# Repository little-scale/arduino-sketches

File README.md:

# arduino-sketches
Arduino and Teensy-based Sketches

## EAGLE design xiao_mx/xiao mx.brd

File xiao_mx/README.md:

A simple, small USB MIDI device using the Seed Studio Xiao M0, the Adafruit Tinyusb library, 5 pots and 6 unstablised mx cherry switches

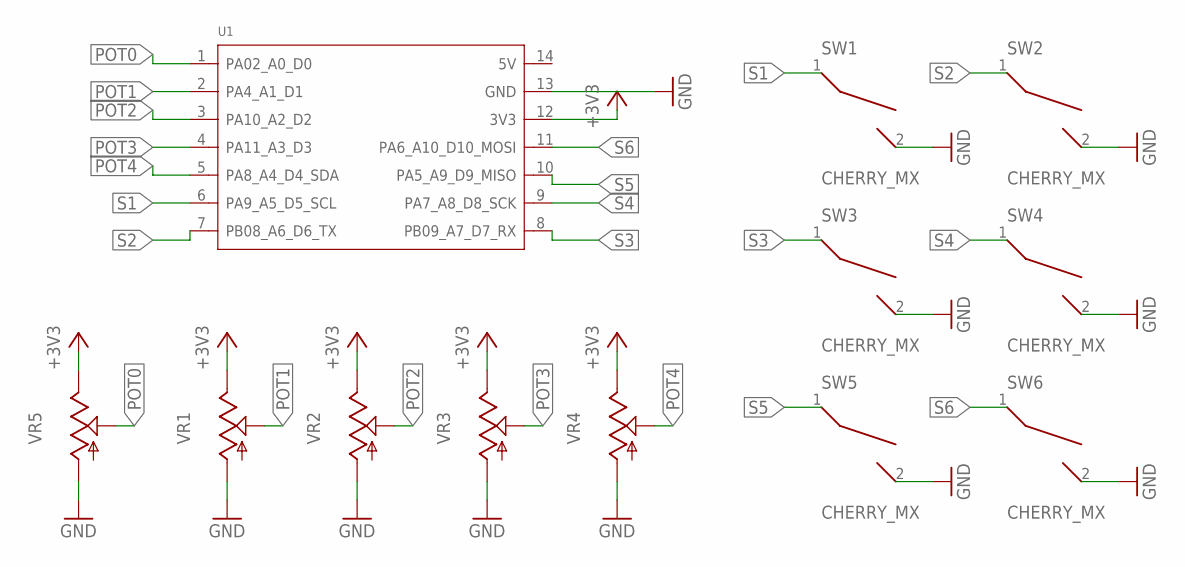
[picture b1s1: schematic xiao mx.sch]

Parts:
SW1, SW2, SW3, SW4, SW5, SW6: CHERRY_MX; MX1A-XXNN
U1: MOUDLE-SEEEDUINO-XIAO; MOUDLE14P-2.54-21X17.8MM
VR1, VR2, VR3, VR4, VR5: 9MM_SNAP-IN_POT_; 9MM_SNAP-IN_POT

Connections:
+3V3: U1.12 (3V3), VR1.3 (E), VR2.3 (E), VR3.3 (E), VR4.3 (E), VR5.3 (E)
GND: SW1.2, SW2.2, SW3.2, SW4.2, SW5.2, SW6.2, U1.13 (GND), VR1.1 (A), VR2.1 (A), VR3.1 (A), VR4.1 (A), VR5.1 (A)
POT0: U1.1 (PA02_A0_D0), VR5.2 (S)
POT1: U1.2 (PA4_A1_D1), VR1.2 (S)
POT2: U1.3 (PA10_A2_D2), VR2.2 (S)
POT3: U1.4 (PA11_A3_D3), VR3.2 (S)
POT4: U1.5 (PA8_A4_D4_SDA), VR4.2 (S)
S1: SW1.1, U1.6 (PA9_A5_D5_SCL)
S2: SW2.1, U1.7 (PB08_A6_D6_TX)
S3: SW3.1, U1.8 (PB09_A7_D7_RX)
S4: SW4.1, U1.9 (PA7_A8_D8_SCK)
S5: SW5.1, U1.10 (PA5_A9_D9_MISO)
S6: SW6.1, U1.11 (PA6_A10_D10_MOSI)

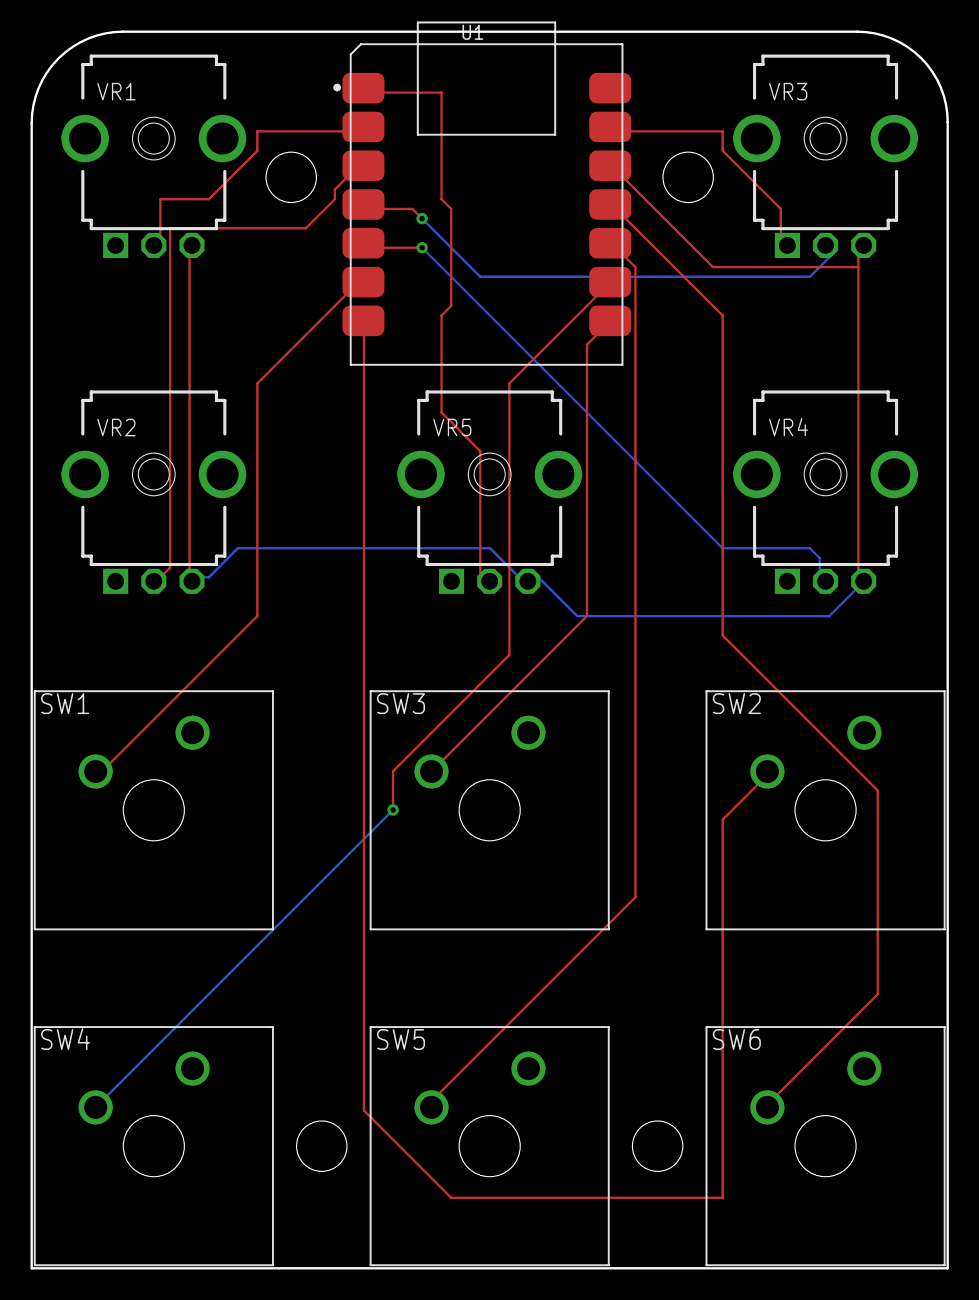
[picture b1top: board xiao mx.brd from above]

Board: 2 copper layers, 60.0 x 81.0 mm, 12 parts (0 on the bottom side), 13 nets.

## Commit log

2020-05-20 Rename footswitch_ethernet.ino to Footswitch_Ethernet.ino
2020-06-02 Rename Distance_Sensor_HCSR04_USB_MIDI_Pitch.ino to Distance_Sensor_HCSR04_3_USB_MIDI_Pitch.ino
